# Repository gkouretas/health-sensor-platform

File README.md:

# health-sensor-platform
Senior capstone project for wearable health sensor and desktop user interface connectable via Bluetooth

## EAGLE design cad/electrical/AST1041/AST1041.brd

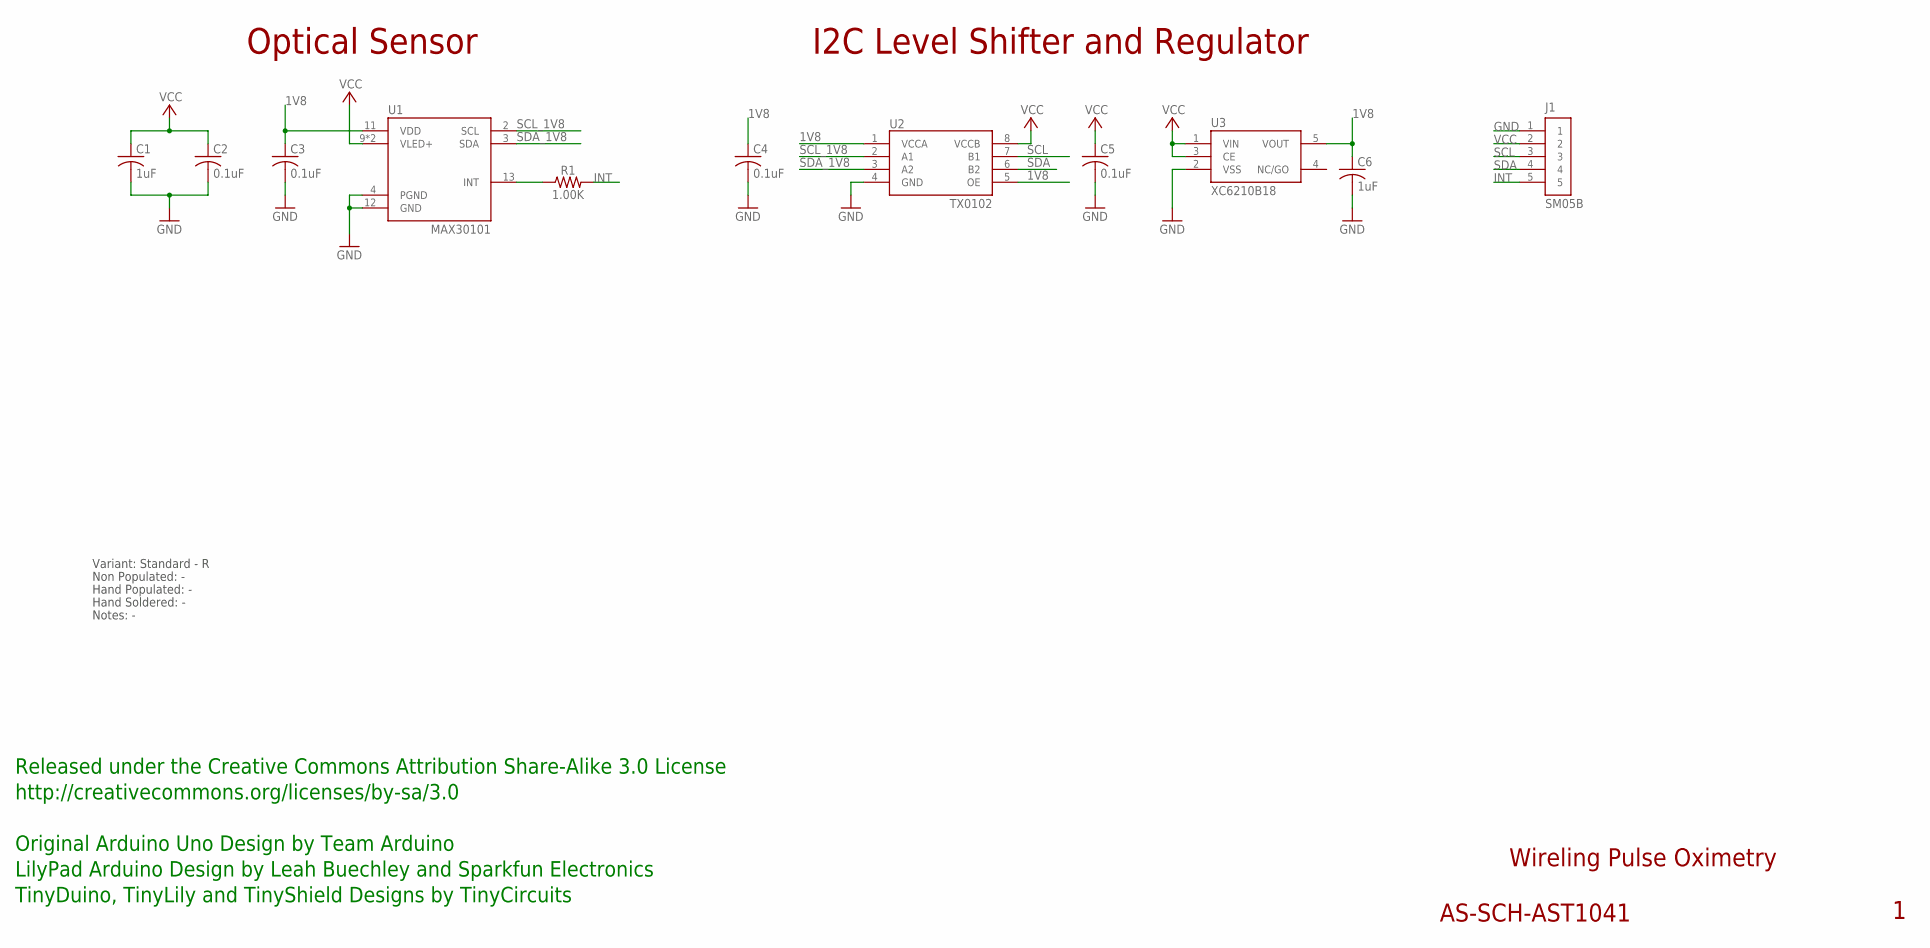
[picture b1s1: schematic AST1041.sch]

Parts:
C1, C6: 1uF; C0402; PARTNO AS-ITM-00105
C2: 0.1uF; C0402
C3, C4, C5: 0.1uF; C0402; PARTNO AS-ITM-00008
J1: SM05B; JST_SH_5X1_EDGE
R1: 1.00K; 0402
U1: MAX30101; MAX30100
U2: TX0102; DQE(R-PX2SON-N8)
U3: XC6210B18; SOT-25

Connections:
1V8: C3.1, C4.1, C6.1, U1.11 (VDD), U2.1 (VCCA), U2.5 (OE), U3.5 (VOUT)
GND: C1.2, C2.2, C3.2, C4.2, C5.2, C6.2, J1.1, U1.4 (PGND), U1.12 (GND), U2.4 (GND), U3.2 (VSS)
INT: J1.5, R1.2
unnamed: R1.1, U1.13 (INT)
SCL: J1.3, U2.7 (B1)
SCL_1V8: U1.2 (SCL), U2.2 (A1)
SDA: J1.4, U2.6 (B2)
SDA_1V8: U1.3 (SDA), U2.3 (A2)
VCC: C1.1, C2.1, C5.1, J1.2, U1.9 (VLED+), U1.10 (VLED+), U2.8 (VCCB), U3.1 (VIN), U3.3 (CE)

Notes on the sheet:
Wireling Pulse Oximetry
AS-SCH-AST1041
Optical Sensor
Released under the Creative Commons Attribution Share-Alike 3.0 License
http://creativecommons.org/licenses/by-sa/3.0
Original Arduino Uno Design by Team Arduino
TinyDuino, TinyLily and TinyShield Designs by TinyCircuits
LilyPad Arduino Design by Leah Buechley and Sparkfun Electronics
I2C Level Shifter and Regulator
Non Populated: -
Hand Populated: -
Hand Soldered: -
Notes: -
Variant: Standard - R

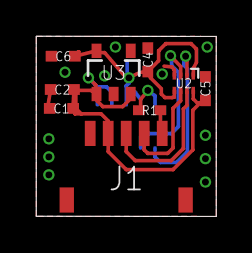
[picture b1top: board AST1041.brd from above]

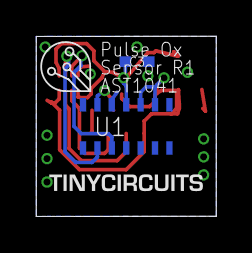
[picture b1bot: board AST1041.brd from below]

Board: 2 copper layers, 10.0 x 10.0 mm, 12 parts (2 on the bottom side), 9 nets.

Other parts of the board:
U$1: DOCFIELD-TINYCIRCUITS-PCB

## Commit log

2021-12-28 Added menu inputs and dropdowns
2021-12-28 Made functional page for user creation
2021-12-31 Created ability to add users and store their info
2022-01-03 Changed callbacks module
2022-01-03 Updated cad files
2022-01-03 Updated alias names
2022-01-04 Updated CAD
2022-01-04 Created Arduino Nano subassembly with headers
2022-01-04 Added protoboard CAD
2022-01-04 Made protoboard subassembly with Arduino
2022-01-04 Fixed Arduino header subassembly
2022-01-04 Added IR sensor CAD
2022-01-05 Created Arduino code directory
2022-01-05 Added custom MAX30101 library derived from Sparkfun
2022-01-05 Added miniboost dxf
2022-01-05 CADchanges
2022-01-05 New changes
2022-01-05 Rendered remaining components
2022-01-05 Updated CAD for components
2022-01-05 Added additional test arduino scripts
2022-01-05 Added MAX30101 user guide
2022-01-05 Changed object name in test scripts
2022-01-05 Updated and added external arduino libraries
2022-01-05 Added Sparkfun MAX3010x library with updated MAX30101 library for green LED function
2022-01-06 Updated arduino folder
2022-01-26 Updated scripts
2022-02-04 Updated temp sensor test script
